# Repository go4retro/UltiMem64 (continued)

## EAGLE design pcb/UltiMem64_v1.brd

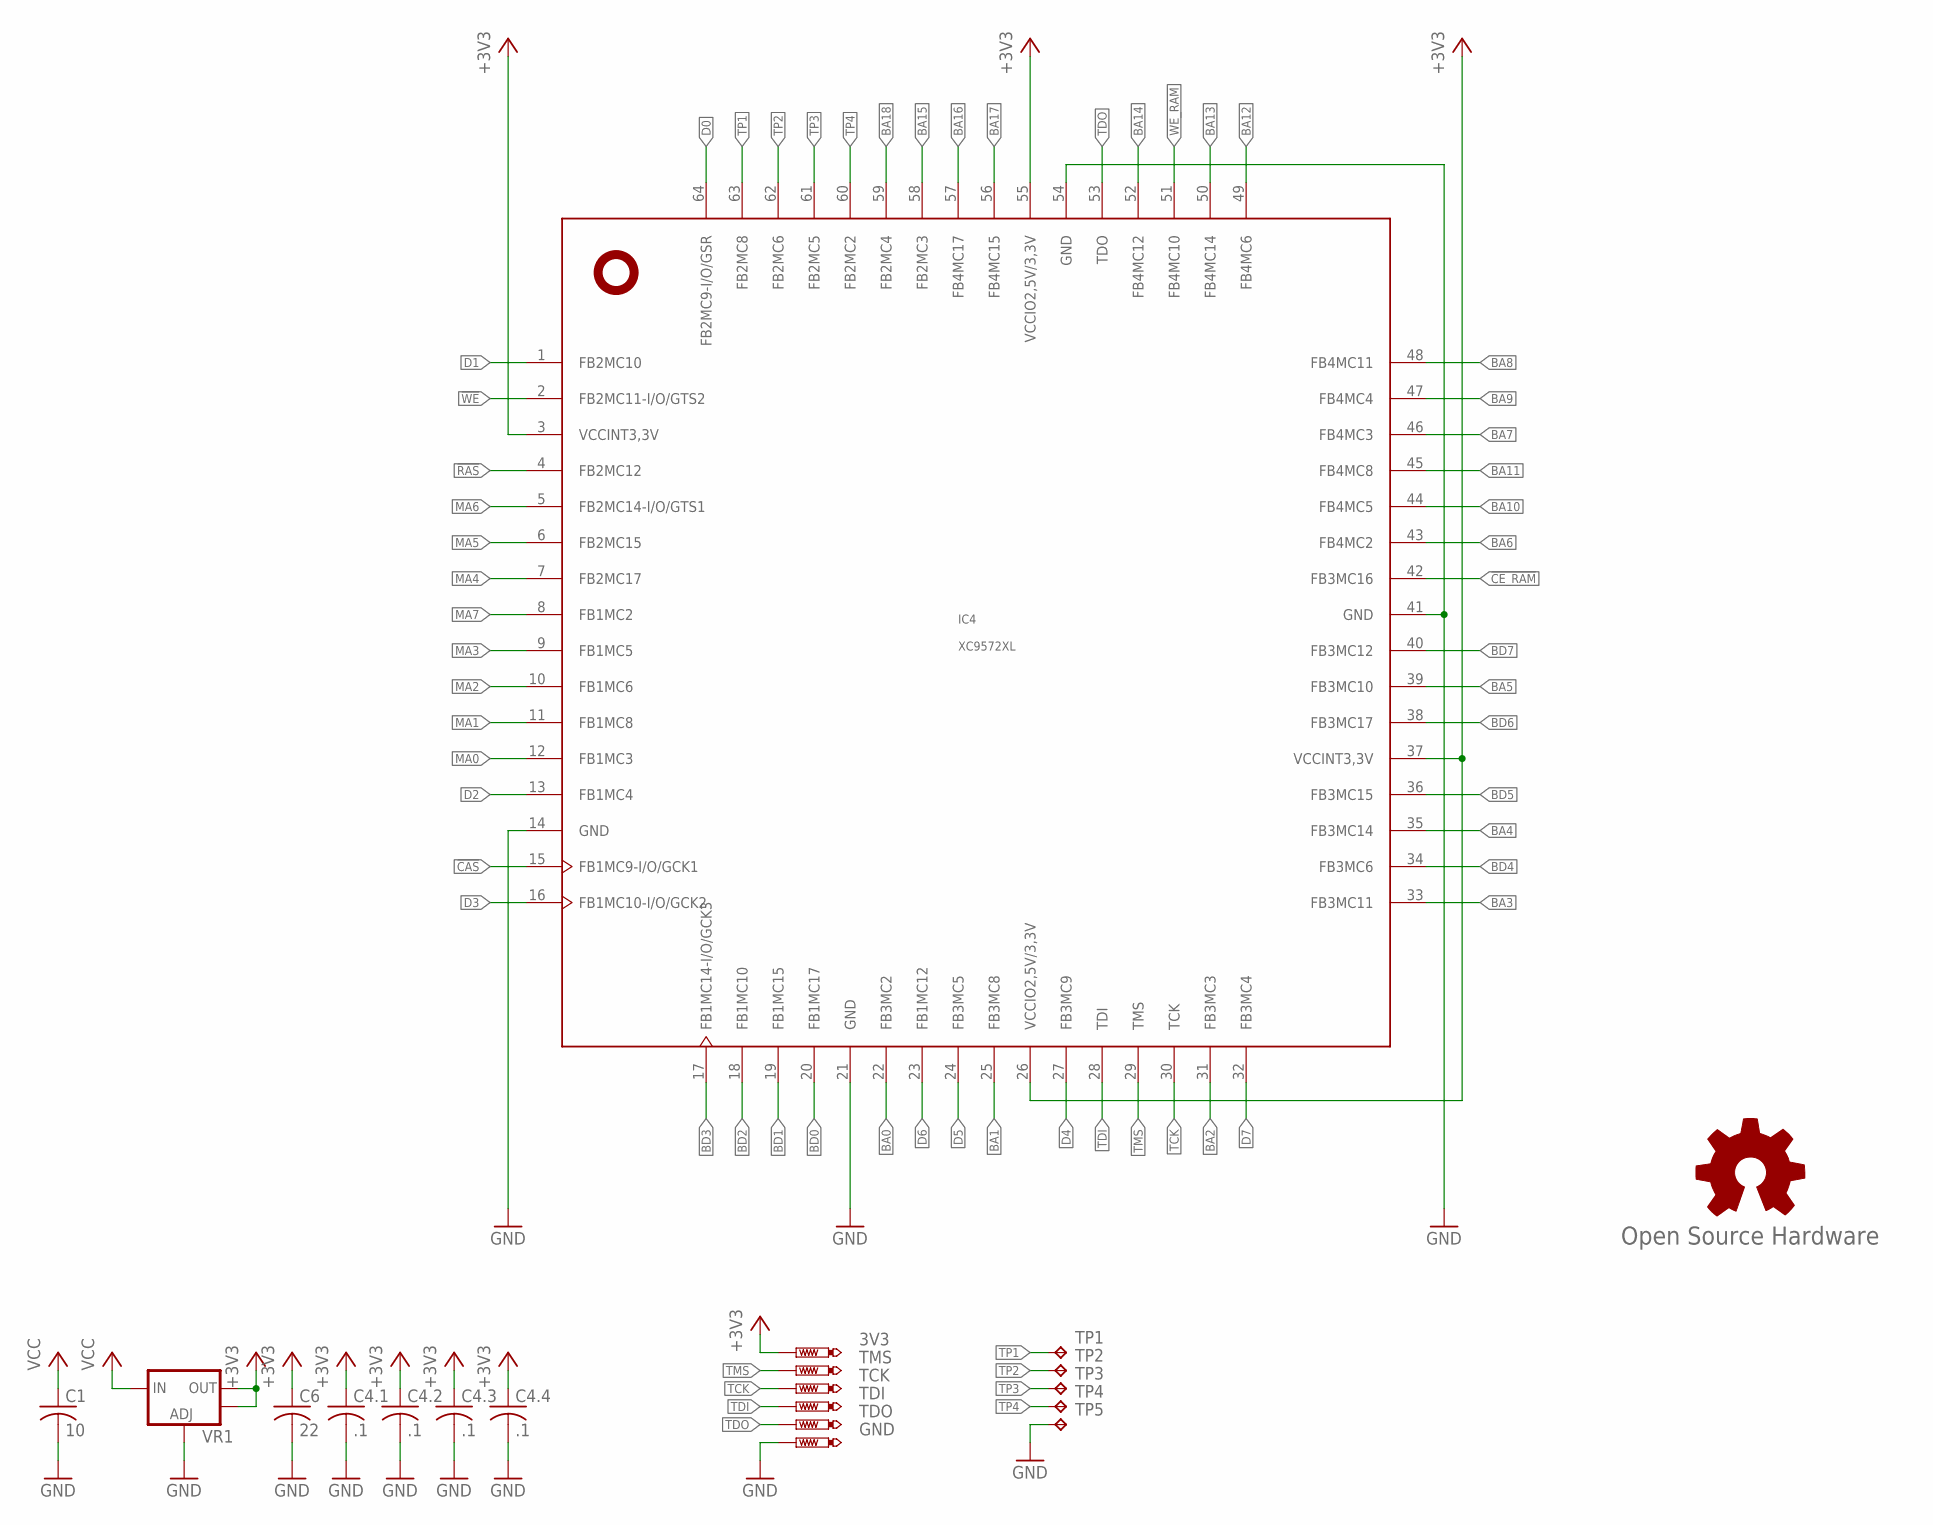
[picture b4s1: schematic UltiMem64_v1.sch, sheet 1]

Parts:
3V3: PTR1TP08R; TP08R
C1: 10; C0805
C4.1, C4.2, C4.3, C4.4: .1; C0402
C6: 22; C0805
GND: PTR1TP08R; TP08R
GOLD_ORB_SM1: Open Source Hardware; OSHW_5MM
IC4: XC9572XL; VQFP64
TCK: PTR1TP08R; TP08R
TDI: PTR1TP08R; TP08R
TDO: PTR1TP08R; TP08R
TMS: PTR1TP08R; TP08R
TP1, TP2, TP3, TP4, TP5: TPPAD1-13; P1-13
VR1: V_REG_LM1117SOT223; SOT223

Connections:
!CAS: IC4.15 (FB1MC9-I/O/GCK1); also elsewhere on the board
!CE_RAM: IC4.42 (FB3MC16); also elsewhere on the board
!RAS: IC4.4 (FB2MC12); also elsewhere on the board
!WE: IC4.2 (FB2MC11-I/O/GTS2); also elsewhere on the board
!WE_RAM: IC4.51 (FB4MC10); also elsewhere on the board
+3V3: 3V3.TP, C4.1.1, C4.2.1, C4.3.1, C4.4.1, C6.1, IC4.3 (VCCINT3,3V), IC4.26 (VCCIO2,5V/3,3V), IC4.37 (VCCINT3,3V), IC4.55 (VCCIO2,5V/3,3V), VR1.2 (OUT), VR1.4 (OUT)
BA0: IC4.22 (FB3MC2); also elsewhere on the board
BA1: IC4.25 (FB3MC8); also elsewhere on the board
BA2: IC4.31 (FB3MC3); also elsewhere on the board
BA3: IC4.33 (FB3MC11); also elsewhere on the board
BA4: IC4.35 (FB3MC14); also elsewhere on the board
BA5: IC4.39 (FB3MC10); also elsewhere on the board
BA6: IC4.43 (FB4MC2); also elsewhere on the board
BA7: IC4.46 (FB4MC3); also elsewhere on the board
BA8: IC4.48 (FB4MC11); also elsewhere on the board
BA9: IC4.47 (FB4MC4); also elsewhere on the board
BA10: IC4.44 (FB4MC5); also elsewhere on the board
BA11: IC4.45 (FB4MC8); also elsewhere on the board
BA12: IC4.49 (FB4MC6); also elsewhere on the board
BA13: IC4.50 (FB4MC14); also elsewhere on the board
BA14: IC4.52 (FB4MC12); also elsewhere on the board
BA15: IC4.58 (FB2MC3); also elsewhere on the board
BA16: IC4.57 (FB4MC17); also elsewhere on the board
BA17: IC4.56 (FB4MC15); also elsewhere on the board
BA18: IC4.59 (FB2MC4); also elsewhere on the board
BD0: IC4.20 (FB1MC17); also elsewhere on the board
BD1: IC4.19 (FB1MC15); also elsewhere on the board
BD2: IC4.18 (FB1MC10); also elsewhere on the board
BD3: IC4.17 (FB1MC14-I/O/GCK3); also elsewhere on the board
BD4: IC4.34 (FB3MC6); also elsewhere on the board
BD5: IC4.36 (FB3MC15); also elsewhere on the board
BD6: IC4.38 (FB3MC17); also elsewhere on the board
BD7: IC4.40 (FB3MC12); also elsewhere on the board
D0: IC4.64 (FB2MC9-I/O/GSR); also elsewhere on the board
D1: IC4.1 (FB2MC10); also elsewhere on the board
D2: IC4.13 (FB1MC4); also elsewhere on the board
D3: IC4.16 (FB1MC10-I/O/GCK2); also elsewhere on the board
D4: IC4.27 (FB3MC9); also elsewhere on the board
D5: IC4.24 (FB3MC5); also elsewhere on the board
D6: IC4.23 (FB1MC12); also elsewhere on the board
D7: IC4.32 (FB3MC4); also elsewhere on the board
GND: C1.2, C4.1.2, C4.2.2, C4.3.2, C4.4.2, C6.2, GND.TP, IC4.14 (GND), IC4.21 (GND), IC4.41 (GND), IC4.54 (GND), TP5.TP, VR1.1 (ADJ); also elsewhere on the board
MA0: IC4.12 (FB1MC3); also elsewhere on the board
MA1: IC4.11 (FB1MC8); also elsewhere on the board
MA2: IC4.10 (FB1MC6); also elsewhere on the board
MA3: IC4.9 (FB1MC5); also elsewhere on the board
MA4: IC4.7 (FB2MC17); also elsewhere on the board
MA5: IC4.6 (FB2MC15); also elsewhere on the board
MA6: IC4.5 (FB2MC14-I/O/GTS1); also elsewhere on the board
MA7: IC4.8 (FB1MC2); also elsewhere on the board
TCK: IC4.30 (TCK), TCK.TP
TDI: IC4.28 (TDI), TDI.TP
TDO: IC4.53 (TDO), TDO.TP
TMS: IC4.29 (TMS), TMS.TP
TP1: IC4.63 (FB2MC8), TP1.TP
TP2: IC4.62 (FB2MC6), TP2.TP
TP3: IC4.61 (FB2MC5), TP3.TP
TP4: IC4.60 (FB2MC2), TP4.TP
VCC: C1.1, VR1.3 (IN); also elsewhere on the board

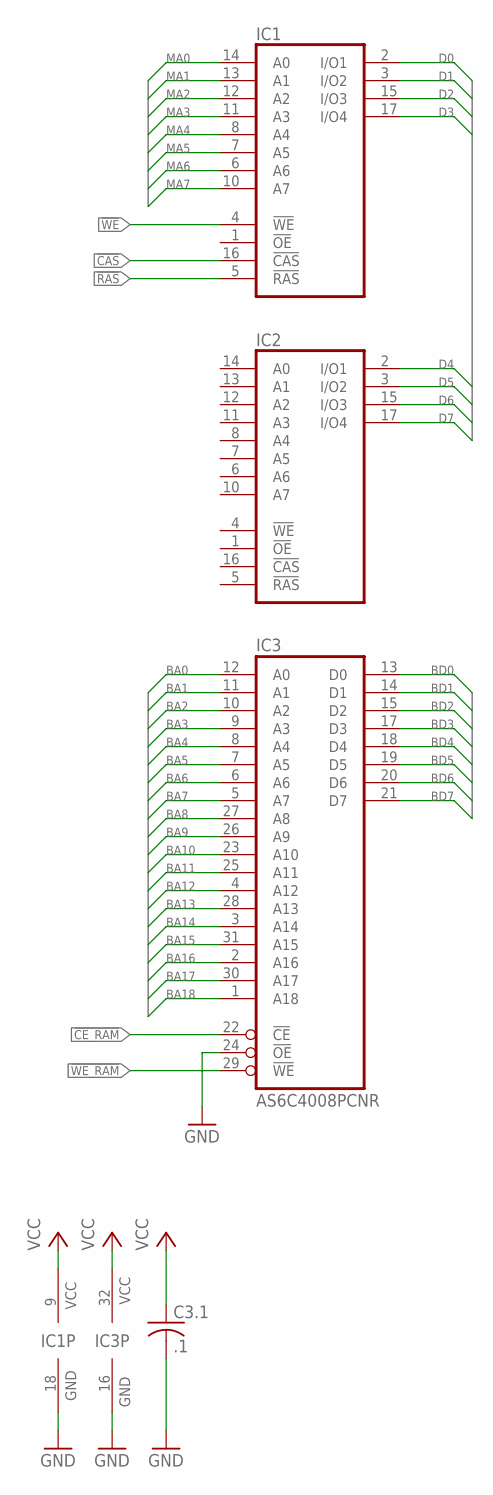
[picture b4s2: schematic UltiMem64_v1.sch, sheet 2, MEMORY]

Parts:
C3.1: .1; C0402
IC1, IC2: 41464C-HDR; DIL18_REV
IC3: AS6C4008PCNR; DIL32-RP

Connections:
!CAS: IC1.16 (!CAS); also elsewhere on the board
!CE_RAM: IC3.22 (!CE); also elsewhere on the board
!RAS: IC1.5 (!RAS); also elsewhere on the board
!WE: IC1.4 (!WE); also elsewhere on the board
!WE_RAM: IC3.29 (!WE); also elsewhere on the board
BA0: IC3.12 (A0); also elsewhere on the board
BA1: IC3.11 (A1); also elsewhere on the board
BA2: IC3.10 (A2); also elsewhere on the board
BA3: IC3.9 (A3); also elsewhere on the board
BA4: IC3.8 (A4); also elsewhere on the board
BA5: IC3.7 (A5); also elsewhere on the board
BA6: IC3.6 (A6); also elsewhere on the board
BA7: IC3.5 (A7); also elsewhere on the board
BA8: IC3.27 (A8); also elsewhere on the board
BA9: IC3.26 (A9); also elsewhere on the board
BA10: IC3.23 (A10); also elsewhere on the board
BA11: IC3.25 (A11); also elsewhere on the board
BA12: IC3.4 (A12); also elsewhere on the board
BA13: IC3.28 (A13); also elsewhere on the board
BA14: IC3.3 (A14); also elsewhere on the board
BA15: IC3.31 (A15); also elsewhere on the board
BA16: IC3.2 (A16); also elsewhere on the board
BA17: IC3.30 (A17); also elsewhere on the board
BA18: IC3.1 (A18); also elsewhere on the board
BD0: IC3.13 (D0); also elsewhere on the board
BD1: IC3.14 (D1); also elsewhere on the board
BD2: IC3.15 (D2); also elsewhere on the board
BD3: IC3.17 (D3); also elsewhere on the board
BD4: IC3.18 (D4); also elsewhere on the board
BD5: IC3.19 (D5); also elsewhere on the board
BD6: IC3.20 (D6); also elsewhere on the board
BD7: IC3.21 (D7); also elsewhere on the board
D0: IC1.2 (I/O1); also elsewhere on the board
D1: IC1.3 (I/O2); also elsewhere on the board
D2: IC1.15 (I/O3); also elsewhere on the board
D3: IC1.17 (I/O4); also elsewhere on the board
D4: IC2.2 (I/O1); also elsewhere on the board
D5: IC2.3 (I/O2); also elsewhere on the board
D6: IC2.15 (I/O3); also elsewhere on the board
D7: IC2.17 (I/O4); also elsewhere on the board
GND: C3.1.2, IC1.18 (GND), IC2.18 (GND), IC3.16 (GND), IC3.24 (!OE); also elsewhere on the board
MA0: IC1.14 (A0); also elsewhere on the board
MA1: IC1.13 (A1); also elsewhere on the board
MA2: IC1.12 (A2); also elsewhere on the board
MA3: IC1.11 (A3); also elsewhere on the board
MA4: IC1.8 (A4); also elsewhere on the board
MA5: IC1.7 (A5); also elsewhere on the board
MA6: IC1.6 (A6); also elsewhere on the board
MA7: IC1.10 (A7); also elsewhere on the board
VCC: C3.1.1, IC1.9 (VCC), IC2.9 (VCC), IC3.32 (VCC); also elsewhere on the board

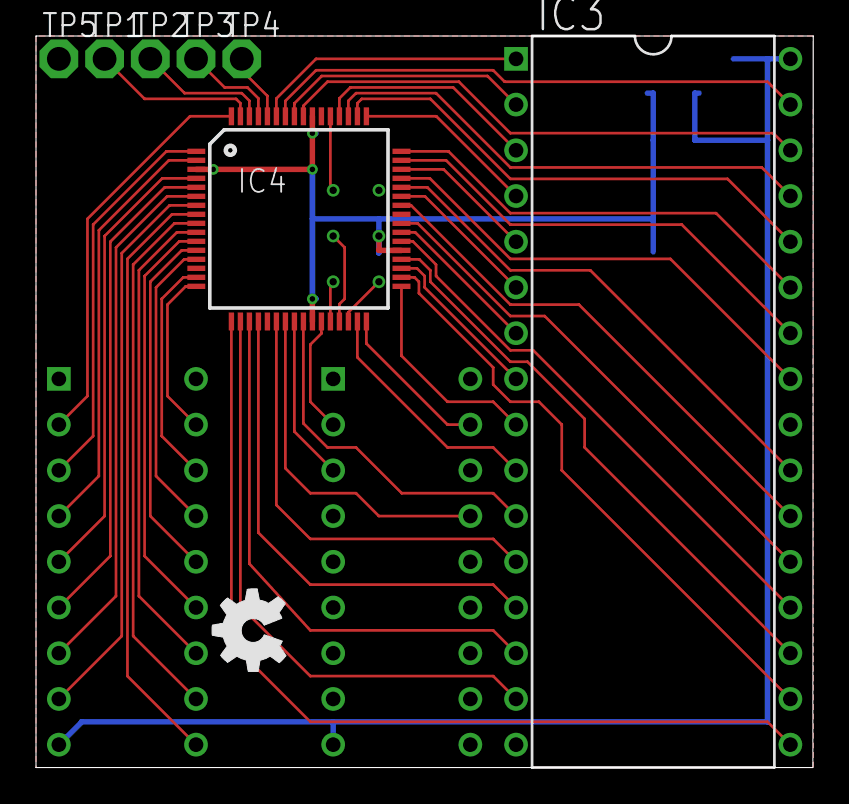
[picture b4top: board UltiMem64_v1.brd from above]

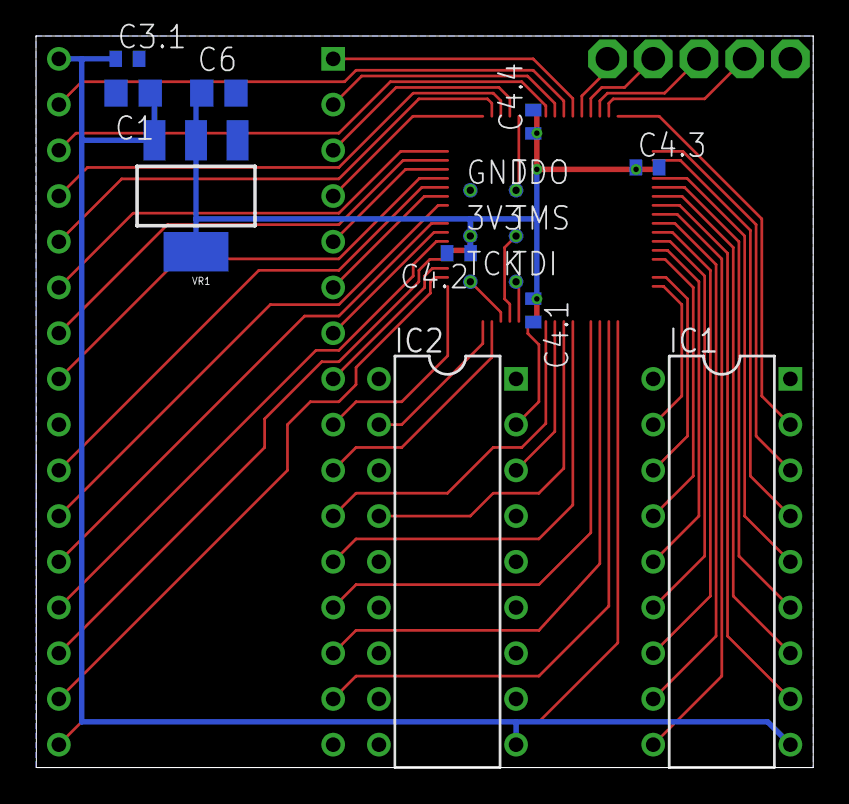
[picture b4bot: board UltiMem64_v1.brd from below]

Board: 2 copper layers, 43.2 x 40.6 mm, 24 parts (14 on the bottom side), 59 nets.

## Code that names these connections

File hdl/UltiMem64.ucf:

#PACE: Start of Constraints generated by PACE

#PACE: Start of PACE I/O Pin Assignments
NET "_cas"  LOC = "P16"  ; 
NET "_ce_ram"  LOC = "P76"  ; 
NET "_ce_tag"  LOC = "p77"  ; 
NET "_lb"  LOC = "p74"  ; 
NET "_ras"  LOC = "P54"  ; 
NET "_reset"  LOC = "p27"  ;
NET "_ub"  LOC = "p72"  ; 
NET "_we"  LOC = "P56"  ; 
NET "_we_mem"  LOC = "P97"  ; 
NET "baddress<0>"  LOC = "P65"  ; 
NET "baddress<10>"  LOC = "P6"  ; 
NET "baddress<11>"  LOC = "P3"  ; 
NET "baddress<12>"  LOC = "P1"  ; 
NET "baddress<13>"  LOC = "P68"  ; 
NET "baddress<14>"  LOC = "P66"  ; 
NET "baddress<15>"  LOC = "P64"  ; 
NET "baddress<16>"  LOC = "P11"  ; 
NET "baddress<17>"  LOC = "P9"  ; 
NET "baddress<18>"  LOC = "P12"  ; 
NET "baddress<19>"  LOC = "p61"  ; 
NET "baddress<1>"  LOC = "P67"  ; 
NET "baddress<20>"  LOC = "p13"  ; 
NET "baddress<2>"  LOC = "P70"  ; 
NET "baddress<3>"  LOC = "P71"  ; 
NET "baddress<4>"  LOC = "P73"  ; 
NET "baddress<5>"  LOC = "P99"  ; 
NET "baddress<6>"  LOC = "P2"  ; 
NET "baddress<7>"  LOC = "P4"  ; 
NET "baddress<8>"  LOC = "P7"  ; 
NET "baddress<9>"  LOC = "P8"  ; 
NET "bdata<0>"  LOC = "P79"  ; 
NET "bdata<10>"  LOC = "p92"  ; 
NET "bdata<11>"  LOC = "p90"  ; 
NET "bdata<12>"  LOC = "p86"  ; 
NET "bdata<13>"  LOC = "p82"  ; 
NET "bdata<14>"  LOC = "p80"  ; 
NET "bdata<15>"  LOC = "p78"  ; 
NET "bdata<1>"  LOC = "P81"  ; 
NET "bdata<2>"  LOC = "P85"  ; 
NET "bdata<3>"  LOC = "P87"  ; 
NET "bdata<4>"  LOC = "P89"  ; 
NET "bdata<5>"  LOC = "P91"  ; 
NET "bdata<6>"  LOC = "P93"  ; 
NET "bdata<7>"  LOC = "P95"  ; 
NET "bdata<8>"  LOC = "p96"  ; 
NET "bdata<9>"  LOC = "p94"  ; 
NET "clock"  LOC = "P22"  ; 
NET "data<0>"  LOC = "P60"  ; 
NET "data<1>"  LOC = "P59"  ; 
NET "data<2>"  LOC = "P46"  ; 
NET "data<3>"  LOC = "P43"  ; 
NET "data<4>"  LOC = "P29"  ; 
NET "data<5>"  LOC = "P30"  ; 
NET "data<6>"  LOC = "P17"  ; 
NET "data<7>"  LOC = "P15"  ; 
NET "maddress<0>"  LOC = "P55"  ; 
NET "maddress<1>"  LOC = "P19"  ; 
NET "maddress<2>"  LOC = "P18"  ; 
NET "maddress<3>"  LOC = "P14"  ; 
NET "maddress<4>"  LOC = "P63"  ; 
NET "maddress<5>"  LOC = "P58"  ; 
NET "maddress<6>"  LOC = "P20"  ; 
NET "maddress<7>"  LOC = "P10"  ; 
#NET "test<1>"  LOC = "p50"  ; 
#NET "test<2>"  LOC = "p49"  ; 
#NET "test<3>"  LOC = "p42"  ; 
#NET "test<4>"  LOC = "p41"  ; 
#NET "test<5>"  LOC = "p33"  ; 
#NET "test<6>"  LOC = "p32"  ; 
#NET "test<7>"  LOC = "p28"  ; 

#PACE: Start of PACE Area Constraints

#PACE: Start of PACE Prohibit Constraints

#PACE: End of Constraints generated by PACE

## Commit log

2019-09-22 Rev 2
2019-09-22 Adding in MMU config capability
2019-09-23 Initial working MMU functionality
2019-10-12 Add in visibility flag
2020-10-16 Added Color RAM functionality
2021-01-28 UltiColorMEM RAM Design
